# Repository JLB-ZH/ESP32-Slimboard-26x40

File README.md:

# ESP32-Slimboard-26x40  
Compact ESP32‑WROOM‑32 slim board (26×40 mm) for vertical or horizontal mounting, with a 10‑pin ZIF for programming and I²C/SPI interface.

## 🧩 The Board

The processor board is made arround the ESPRESSIF ESP32‑WROOM‑32UE with 16 MB of flash (or 32E if no external antenna needed).

USB interface and onboard 3.3V regulator are not provided, an external adapter (see [Tools](#-tools)) can be used for initial programming. OTA updates can be used afterwards.

The board features a 2×15 pin male connector with 2.0 mm pitch, allowing use on prototyping platforms or production boards.

It has been developed with Eagle Cad version 4.16, but Eagle 6 compatible files (XML format) are provided [here](hardware/), and can be easily imported into KICAD.

The mechanical and pinout specifications can apply to many different microcontroller or SOC, including BEKEN BK72xx series, REALTEK RTL8720, if no CANbus needed, just adapt the schematic and use the libraries available in JLB_processor.lbr.

## 📜 Specifications
- Small size: 26x40mm
- 2× holes for 2,5mm screews
- Soc module on-board: ESP32‑WROOM‑32‑E (or UE)
  - 240MHz
  - 16MB Flash
  - 520KB Sram
  - 448 KB Rom
  - CAN 2.0
  - Wifi, Bluetooth
  - many GPIOs
- Externally provided 3.3V power supply
- 1× 2×15×2.0 mm male connector
  - Straight version for horizontal mounting
  - Right‑angle version for vertical mounting  
- Reset button    
- 2× indicators
  - red LED on GPIO0  
  - green LED on GPIO2  
- 1× 1x10x0.5mm ZIF connector 
  - for Jtag or Uart programming (ESPPROG2 + adapter recommended)
  - for I²C or SPI expansion
## 🔌 Connectivity
### main connector
Pins in this table have been assigned to application-specific signals, but all GPIO can be reassigned to other functions by software if necessary.

### Zif connector

## 🖼 Application examples and projects
<table>
  <tr>
    <td><strong>Linky interface</strong></td>
    <td><strong>Tank level Sensor interface</strong></td>
    <td><strong>Prototyping baseboard</strong></td>
  </tr>
  <tr>
    <td></td>
    <td></td>
    <td></td>
  </tr>
</table>

## 📐 Hardware design
Design and library files are provided [here](hardware/) in Eagle 6 format (xml files) that can easily be imported into KICAD.

## 🛠 Tools
|[Uart programming module](https://soldered.com/products/connect-programmer)|[ESPPROG-2 tool](https://docs.espressif.com/projects/esp-dev-kits/en/latest/other/esp-prog-2/user_guide.html)|ZIF programmer|Programming on socket|
|:----------------:|:---------------:|:-------------:|:-------------:|
|||||

## 📑 Table of Contents
- [Processor Board](#-the-board)
- [Software examples](software/arduino/)
- [Hardware](hardware/)
- [Documents](documents/)

## 🛡 Licenses
- [Software](licenses/software/LICENSE-APACHE) : Apache-2.0
- [Hardware](licenses/hardware/LICENSE-CERN-OHL-S) : CERN-OHL-S v2

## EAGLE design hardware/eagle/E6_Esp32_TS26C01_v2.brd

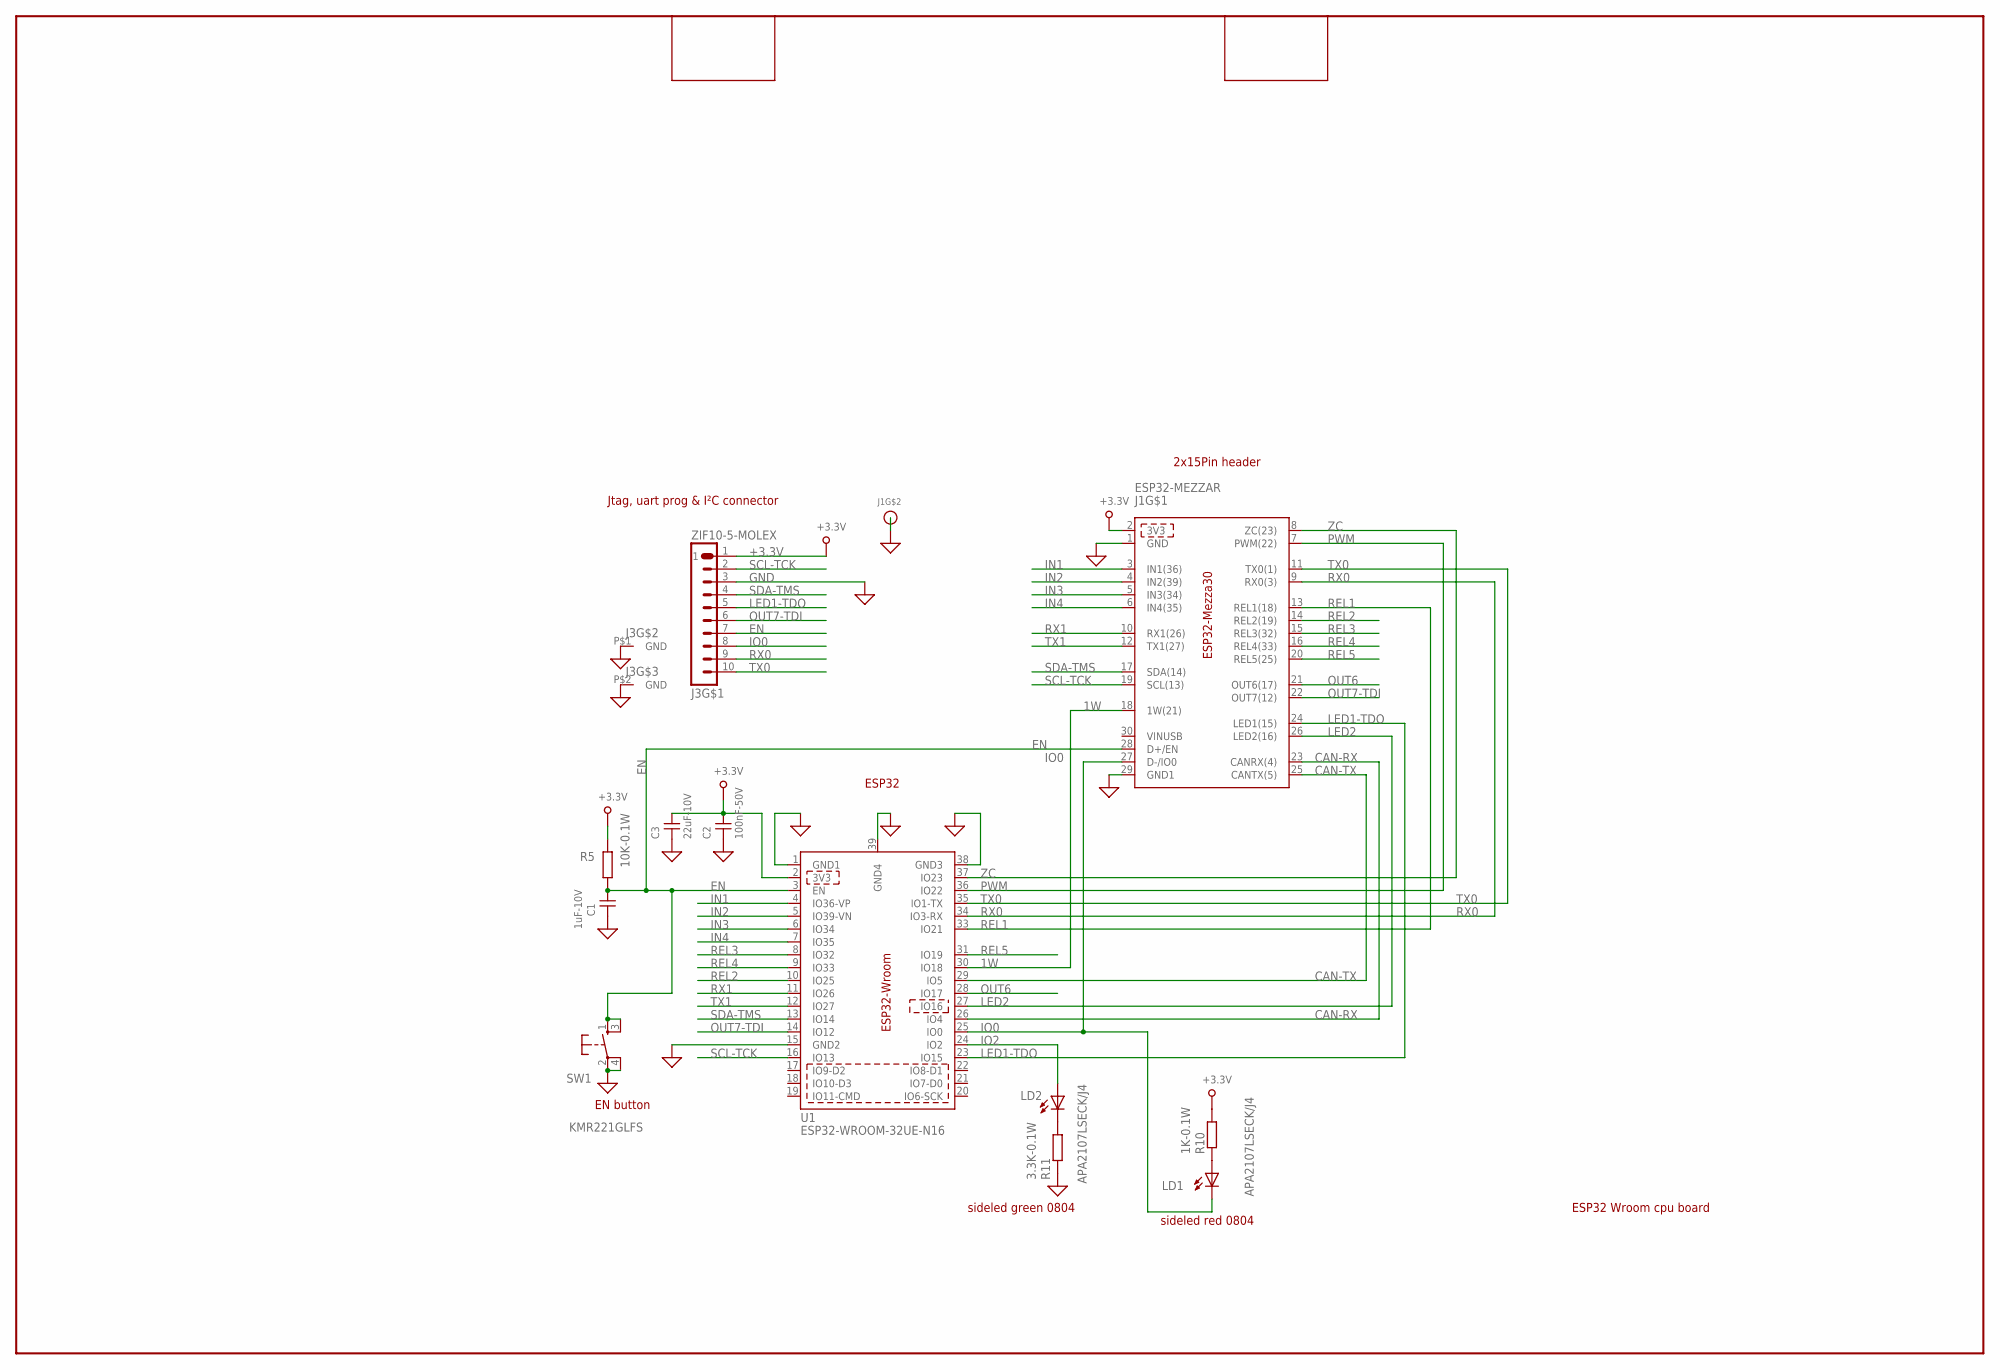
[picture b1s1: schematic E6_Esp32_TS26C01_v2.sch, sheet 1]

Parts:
C1: 1uF-10V; C0603
C2: 100nF-50V; C0603
C3: 22uF-10V; C0603
J1: ESP32-MEZZAR; ESP32-MEZZA25-R
J3: ZIF10-5-MOLEX; 52746-1071-J
LD1, LD2: APA2107LSECK/J4; SIDELED_0805
R5: 10K-0.1W; 0603
R10: 1K-0.1W; 0603
R11: 3.3K-0.1W; 0603
SW1: KMR221GLFS; SW-KMS-HOLE-NOGND
U1: ESP32-WROOM-32UE-N16; ESP32-WROOM-32UE

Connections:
1W: J1.18 (1W(21)), U1.30 (IO18)
+3.3V: C2.2, C3.2, J1.2 (3V3), J3.1, R5.1, R10.1, U1.2 (3V3)
CAN-RX: J1.23 (CANRX(4)), U1.26 (IO4)
CAN-TX: J1.25 (CANTX(5)), U1.29 (IO5)
EN: C1.2, J1.28 (D+/EN), J3.7, R5.2, SW1.1 (S), SW1.3 (S), U1.3 (EN)
GND: C1.1, C2.1, C3.1, J1.1 (GND), J1.29 (GND1), J1.31, J3.3, J3.P$1 (GND), J3.P$2 (GND), J3.P$3 (GND), J3.P$5 (GND), R11.2, SW1.2, SW1.4, U1.1 (GND1), U1.15 (GND2), U1.38 (GND3), U1.39 (GND4)
IN1: J1.3 (IN1(36)), U1.4 (IO36-VP)
IN2: J1.4 (IN2(39)), U1.5 (IO39-VN)
IN3: J1.5 (IN3(34)), U1.6 (IO34)
IN4: J1.6 (IN4(35)), U1.7 (IO35)
IO0: J1.27 (D-/IO0), J3.8, LD1.C, U1.25 (IO0)
IO2: LD2.A, U1.24 (IO2)
LED1-TDO: J1.24 (LED1(15)), J3.5, U1.23 (IO15)
LED2: J1.26 (LED2(16)), U1.27 (IO16)
unnamed: LD1.A, R10.2
unnamed: LD2.C, R11.1
OUT6: J1.21 (OUT6(17)), U1.28 (IO17)
OUT7-TDI: J1.22 (OUT7(12)), J3.6, U1.14 (IO12)
PWM: J1.7 (PWM(22)), U1.36 (IO22)
REL1: J1.13 (REL1(18)), U1.33 (IO21)
REL2: J1.14 (REL2(19)), U1.10 (IO25)
REL3: J1.15 (REL3(32)), U1.8 (IO32)
REL4: J1.16 (REL4(33)), U1.9 (IO33)
REL5: J1.20 (REL5(25)), U1.31 (IO19)
RX0: J1.9 (RX0(3)), J3.9, U1.34 (IO3-RX)
RX1: J1.10 (RX1(26)), U1.11 (IO26)
SCL-TCK: J1.19 (SCL(13)), J3.2, U1.16 (IO13)
SDA-TMS: J1.17 (SDA(14)), J3.4, U1.13 (IO14)
TX0: J1.11 (TX0(1)), J3.10, U1.35 (IO1-TX)
TX1: J1.12 (TX1(27)), U1.12 (IO27)
ZC: J1.8 (ZC(23)), U1.37 (IO23)

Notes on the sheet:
ESP32 Wroom cpu board
ESP32
2x15Pin header
EN button
sideled red 0804
sideled green 0804
Jtag, uart prog & I²C connector

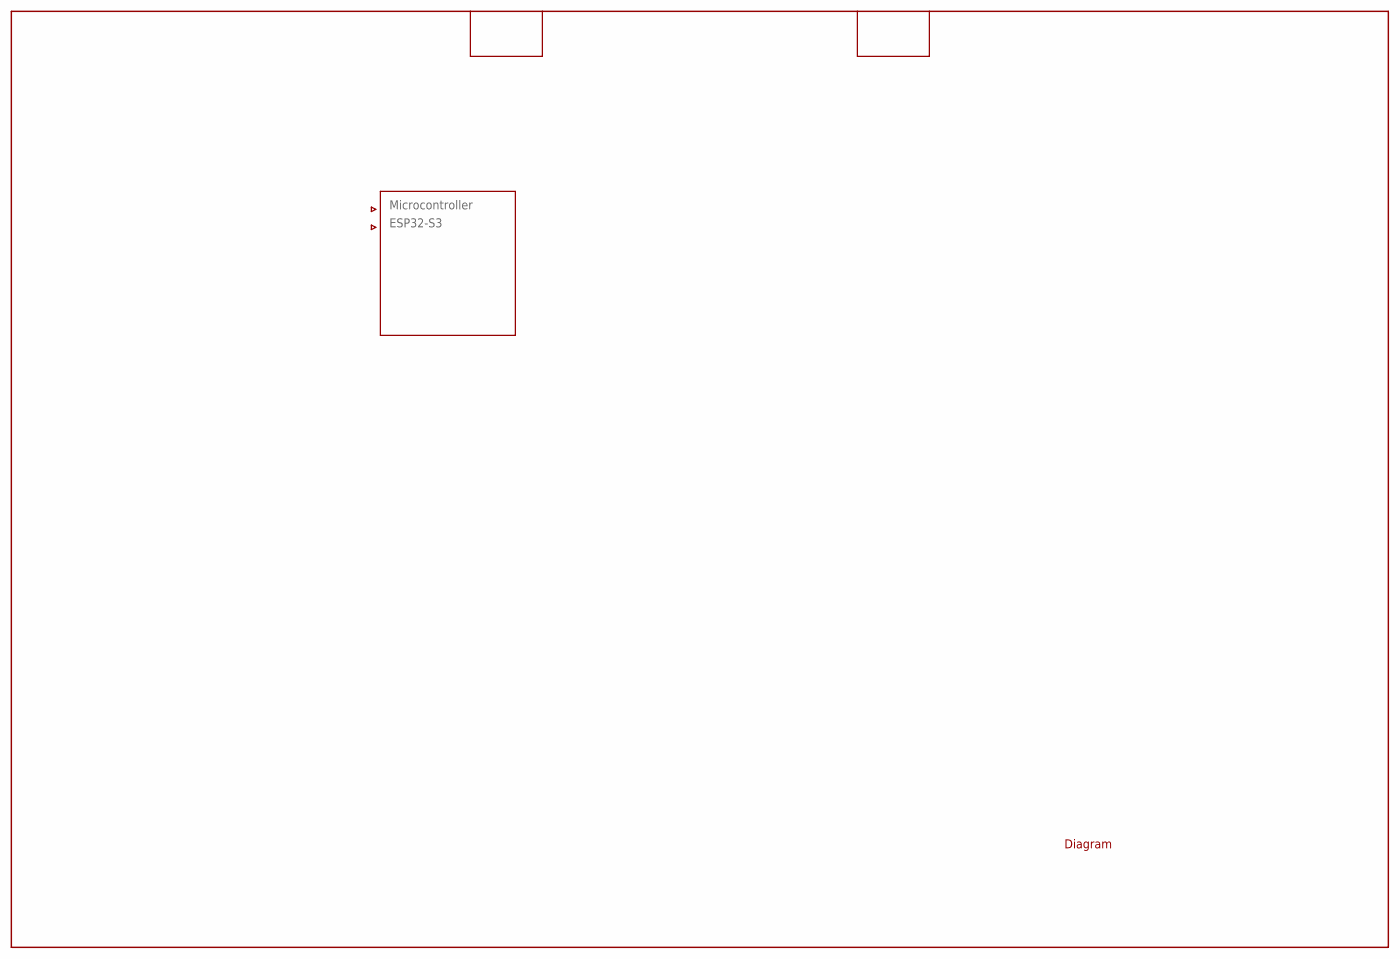
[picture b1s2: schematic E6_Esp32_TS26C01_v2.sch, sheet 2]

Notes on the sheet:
Diagram
Microcontroller
ESP32-S3

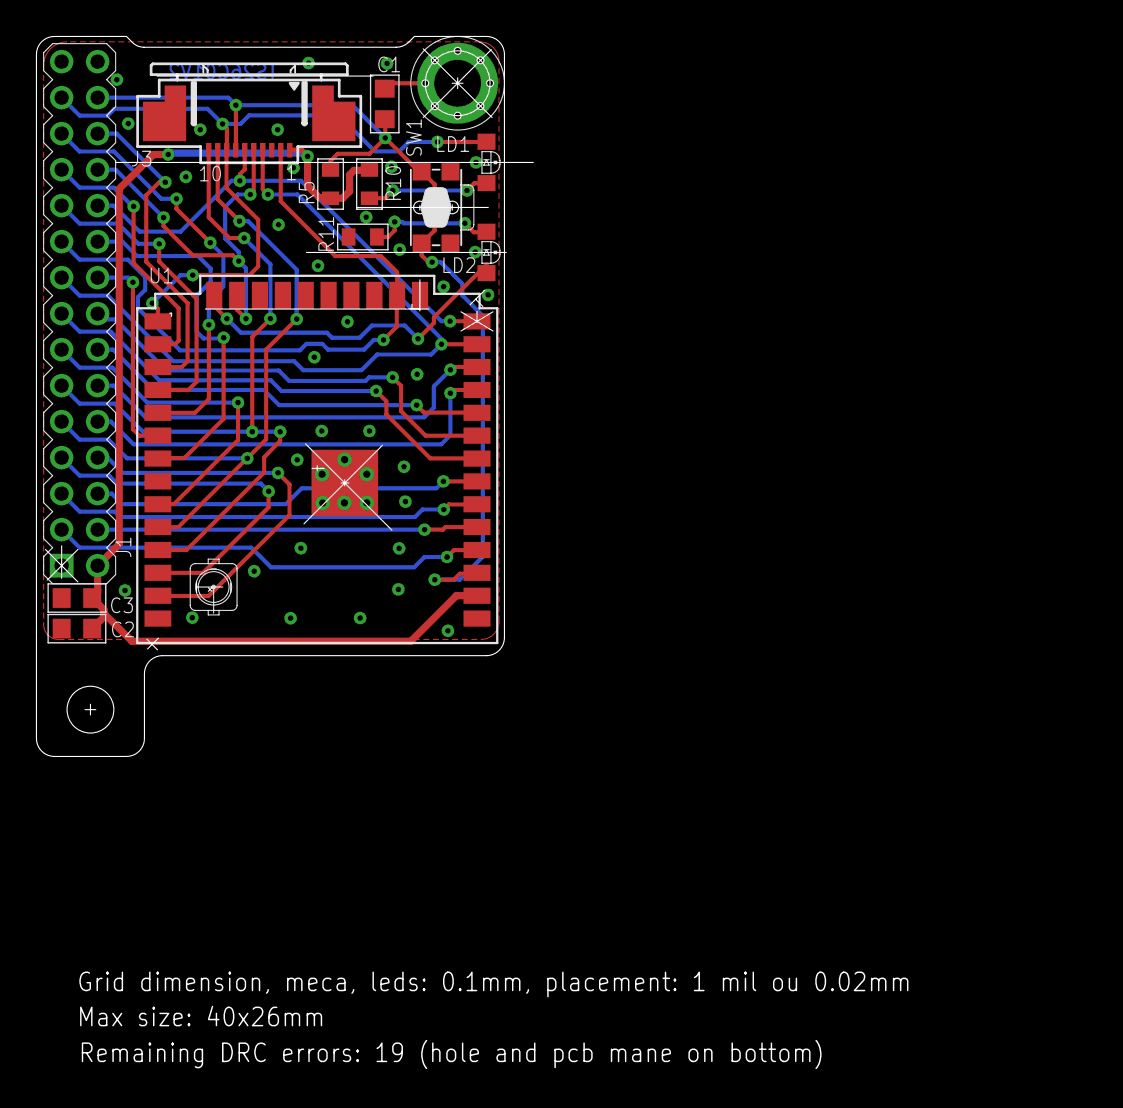
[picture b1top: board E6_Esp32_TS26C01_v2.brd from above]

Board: 2 copper layers, 27.6 x 40.0 mm, 12 parts (0 on the bottom side), 31 nets.
